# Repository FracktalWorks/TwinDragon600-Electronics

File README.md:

# TwinDragon600-Electronics

### For the Combination of BTT Manta M5P + BTT CB1 + BTT EBB36 + MKS Gen L V2.1

Electronic description, pinout and manuals for the electronics used in Twin Dragon 600

Pin Configurations, jumper selection, CanBus and multi-MCU wiring to BTT CB1 embedded onto BTT Manta M5P for Twin Dragon 600

Components used:
1. BTT Manta M5P - 1
2. BTT CB1 (embed onto BTT Manta M5P) - 1
3. BTT EBB36 Can Module/Toolboard - 2
4. TMC5160 Stepper drivers - 5
5. MKS Gen L V2.1 - 1
6. TMC2209 stepper drivers - 2 (On the MKS GenL) + 2 (Present on the BTT EBB36's)
7. BTT HDMI5 Touch Display

### For the Combination of BTT Manta M8P + BTT CB1 + RP2040 based toolboard

Pin Configurations, jumper selection, CanBus and multi-MCU wiring to BTT CB1 embedded onto BTT Manta M8P for Twin Dragon 600

Components used:
1. BTT Manta M8P - 1
2. BTT CB1 (embed onto BTT Manta M8P) - 1
3. RP2040 based Can Module/Toolboard - 2
4. TMC5160 Stepper drivers - 5
5. TMC2209 stepper drivers - 2 (On the MKS GenL) + 2 (Present on the Toolboards)
6. BTT HDMI5 Touch Display

## Setting up BTT Manta M5P + BTT CB1 + BTT EBB36 + MKS Gen L V2.1

### Initial Preparation

At the Initial stage, when needed to only access the CB1 module with USB power supply, a jumper is to be placed in the slot mentioned as 'VUSB' present between the micro HDMI port and the SOC-SD card slot.

This should not be inserted when the board is supplied with 24V and fully functioning.

### Other Initial preparation and setting up jumpers

#### TMC Driver SPI Mode

The first row are the defined pin for the drivers, which are either high or low when shorted or unshorted to establish different mode of communication. The second row are defined with the SPI modes, with the namings of 'MISO', 'CS', 'SCK' and 'MOSI' when read from left to right. Since we use the TMC5160 driver, it specifically operates only on the SPI mode. Insert the jumpers corresponding to its parallel pins only on the 1st and the 2nd row as shown in the image.

#### Driver Voltage selection

Since the TMC5160 operates only on SPI mode, which is specifically for achieving faster communication and higher speeds, it needs an operating voltage of around 48V. The manta M5P has seperte pins for regular voltage of 24V and high voltage of 48V, that is to be jumped to the common pin of voltage supply to the drivers. We jump the HV pin in the left to the middle pin of supply in order to provide 48V to the drivers, as shown in the image above.

#### Setting up jumper for probe activation

The pin for probe used here is the IND-probe pin on Manta M5P, and the jumper is placed on the two pins beside the probe pins as shown in the image above, to enable 24V supply to the ABL board.

#### Setting up Jumper for CANBUS communication

At the bottom-left corner of the board, a small jumper is to be placed on the pins that mention '120R' depicting the 120 ohms resistance that is applied on the CAN Low and High communication pins. This is a crucial pin for the setting up of the CAN communication of the motherboard and toolboard.

## Setting up of BTT EBB36 CAN module/Toolboard

### Initial preparation

After the motherboard is powered on, the yellow-green LED1 lights will light up, indicating a normal power supply. The VUSB on the right side of the board is the power selection terminal. Only when using USB to supply power to the motherboard or need to supply power through USB, do you need to use the jumper cap to connect VUSB.

#### Setting up Jumper for CANBUS communication

Similar to the BTT Manta M5P, the Support communication via CAN or USB. The terminal resistor 120R of CAN can be selected through a jumper cap, and it reserves a CAN expansion interface.

#### Placing of Heatsink

Place the Heatsink onto the TMC2209 driver chip present on the board which is already embedded onto it as shown in the image above.

## Setting up of MKS GenL V2.1 for side extruder motors

### Setting up jumpers for enabling UART mode

Since we use the TMC2209 for the side extruder motors similar to the main extruder motors, we set the drivers in UART mode

## Wiring and Connections

The overall connections of all the Electrical and Electronic components are present in the image above

### BTT Manta M5P Pin connections

### EBB36 Pin connections

The setting up of CANBUS communication in the right angle to avoid confusion

### MKS GenL V2.1 Pin Conections

In the above image, the pin connections of side extruder motors are given, along with additional ports for the extruder filament sensors

## Setting up BTT Manta M8P + BTT CB1 + RP2040 based toolboard

### Initial Preparation

At the Initial stage, when needed to only access the CB1 module with USB power supply, a jumper is to be placed in the slot mentioned as 'VUSB' present behind the Type-C port. After the M8P motherboard is powered on, the D32 red light on the left side of the MCU will light up, indicating that the power supply is normal.

### Other Initial preparation and setting up jumpers

#### TMC Driver SPI Mode

The first row are the defined pin for the drivers, which are either high or low when shorted or unshorted to establish different mode of communication. The second row are defined with the SPI modes, with the namings of 'MISO', 'CS', 'SCK' and 'MOSI' when read from left to right. Since we use the TMC5160 driver, it specifically operates only on the SPI mode. Insert the jumpers corresponding to its parallel pins only on the 1st and the 2nd row as shown in the image.

#### TMC Driver UART Mode

The given set of pin to short is the CS pin that enables only the uart mode.

#### Driver Voltage selection

For High Voltage selection(48V):

Since the TMC5160 operates only on SPI mode, which is specifically for achieving faster communication and higher speeds, it needs an operating voltage of around 48V. The manta M8P has seperte pins for regular voltage of 24V and high voltage of 48V, that is to be jumped to the common pin of voltage supply to the drivers. We jump the HV pin in the left to the middle pin of supply in order to provide 48V to the drivers, as shown in the image above.

For normal Voltage selection (24V):

This voltage selection can be used when using a regular TMC2209 on the UART mode

#### Setting up jumper for probe activation

The pin for probe used here is the IND-probe pin on Manta M8P, and the jumper is placed on the two pins beside the probe pins as shown in the image above, to enable 24V supply to the ABL board.

#### Setting up Jumper for CANBUS communication

At the top of the two CAN pins, a small jumper is to be placed on the pins that mention '120R' depicting the 120 ohms resistance that is applied on the CAN Low and High communication pins. This is a crucial pin for the setting up of the CAN communication of the motherboard and toolboard.

## Setting up of RP2040 based CAN module/Toolboard

After the motherboard is powered on, the green LED light will light up, indicating a normal power supply. The VBUS on the right side of the board is the power selection terminal. Only when using USB to supply power to the motherboard or need to supply power through USB, do you need to use the jumper cap to connect VBUS.

Similar to the BTT Manta M8P, the Support communication via CAN or USB. The terminal resistor 120R of CAN can be selected through a jumper cap, and it reserves a CAN expansion interface.

## Wiring and Connections

The overall connections of all the Electrical and Electronic components are present in the image above

  ### BTT Manta M8P Pin connections

## Setting up BTT Manta M8P V2.0 + RPi CM4 + RP2040 based toolboard

After powering on the M8P, the LED on the bottom left corner will light up to indicate normal power supply. The VUSB jumper in the center is for selecting power - it should only be shorted when powering the board via USB or supplying power out via USB.

### Other Initial preparation and setting up jumpers

#### TMC Driver SPI Mode

The first row are the defined pin for the drivers, which are either high or low when shorted or unshorted to establish different mode of communication. The second row are defined with the SPI modes, with the namings of 'MISO', 'CS', 'SCK' and 'MOSI' when read from left to right. Since we use the TMC5160 driver, it specifically operates only on the SPI mode. Insert the jumpers corresponding to its parallel pins only on the 1st and the 2nd row as shown in the image.

#### TMC Driver UART Mode

The given set of pin to short is the CS pin that enables only the uart mode.

#### Driver Voltage selection

For High Voltage selection(48V):

Since the TMC5160 operates only on SPI mode, which is specifically for achieving faster communication and higher speeds, it needs an operating voltage of around 48V. The manta M8P has seperte pins for regular voltage of 24V and high voltage of 48V, that is to be jumped to the common pin of voltage supply to the drivers. We jump the HV pin in the left to the middle pin of supply in order to provide 48V to the drivers, as shown in the image above.

For normal Voltage selection (24V):

This voltage selection can be used when using a regular TMC2209 on the UART mode

#### Setting up jumper for probe activation

The pin for probe used here is the IND-probe pin on Manta M8P V2.0, and the jumpers are placed on the two pins beside the probe pins, and other three perpendicular pins to its right, where the top two are to jumped together to activate the probe pin, as shown in the image above, to enable 24V/5V supply to the ABL board. The three columns of the pins starting from the top are 5V, 12V, 24V Respectively.

#### Setting up Jumper for CANBUS communication

At the left of the CAN pin, a small jumper is to be placed on the pins that mention '120R' depicting the 120 ohms resistance that is applied on the CAN Low and High communication pins. This is a crucial pin for the setting up of the CAN communication of the motherboard and toolboard.

## Wiring and Connections

The overall connections of all the Electrical and Electronic components are present in the image above

### BTT Manta M8P V2.0 Pin connections

## To setup Raspeberry Pi camera Rev 1.3, interfaced with RPi CM4 and BTT Manta M8P/M5P

In order to interface the Pi camera Rev 1.3 with the RPi CM4 and BTT Manta M8P/M5P, flip the board and check for a CSI1 camera slot, which should look like the image below

Instructions to attach the camera in BTT Manta M8P V2.0

Instructions to attach the camera in BTT Manta M5P

1. Now, boot up the board (including CM4), SSH into the CM4 and open the terminal
2. We will have to download a bin file into the boot folder of the CM4, below is the command to enter into the terminal.

`sudo wget https://datasheets.raspberrypi.com/cmio/dt-blob-cam1.bin -O /boot/dt-blob.bin`

If the above command does not work, try the following command:

`sudo wget https://datasheets.raspberrypi.com/cmio/dt-blob-cam1.bin -O /boot/firmware/dt-blob.bin`

3. Now, in the terminal, enter `sudo raspi-config` and select the option '3 Interface Options    Configure connections to peripherals'. Now select the first option 'P1 Camera      Enable/disable connection to the Raspberry Pi Camera'. A pop-up would appear where it asks to enable the camera. Make sure to select <yes> and exit the portal.

4. Now, in the terminal, type in `sudo nano /boot/config.txt` and make sure the settings are enabled

   `start_x=1
   gpu_mem=128`

   Note: make sure `#camera_auto_select=1` is commented out, or else it will not work.

For more clarifications, check out 'Julia TouchUI documentation' for more settings on Pi-camera

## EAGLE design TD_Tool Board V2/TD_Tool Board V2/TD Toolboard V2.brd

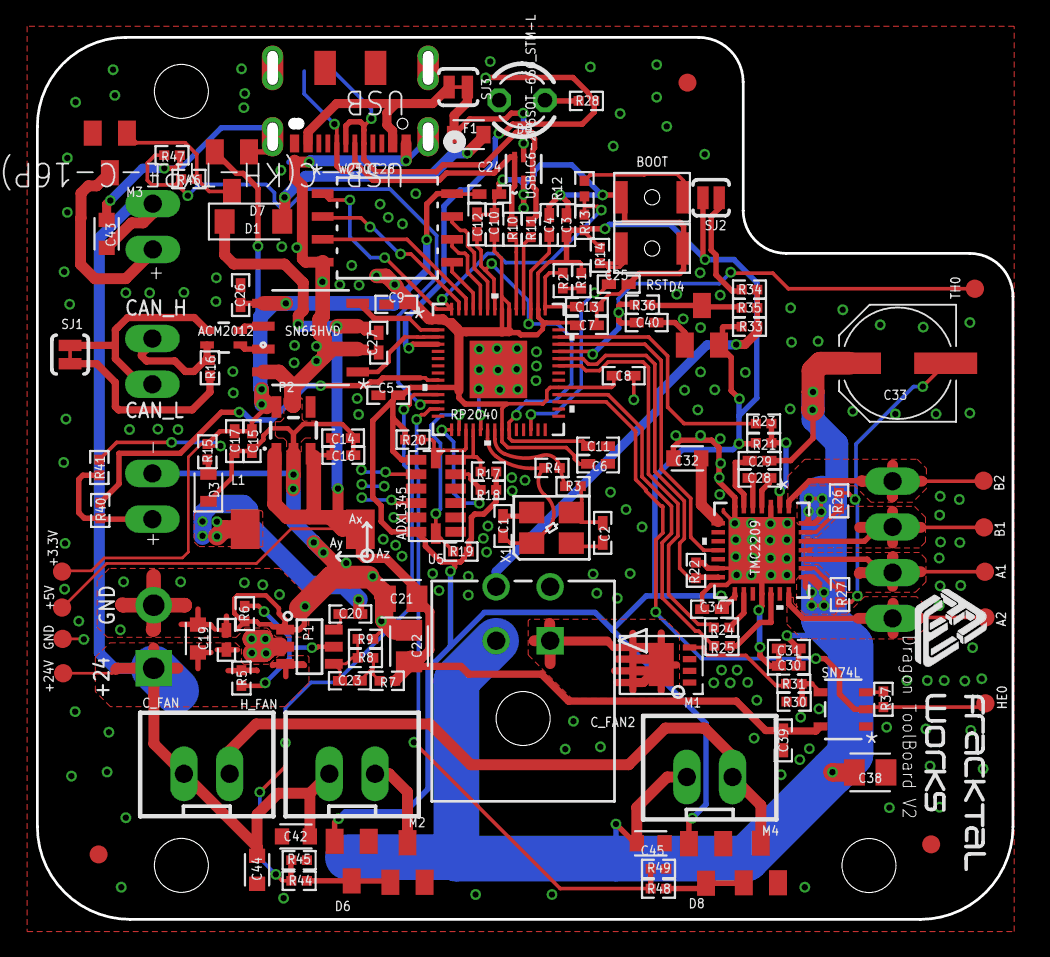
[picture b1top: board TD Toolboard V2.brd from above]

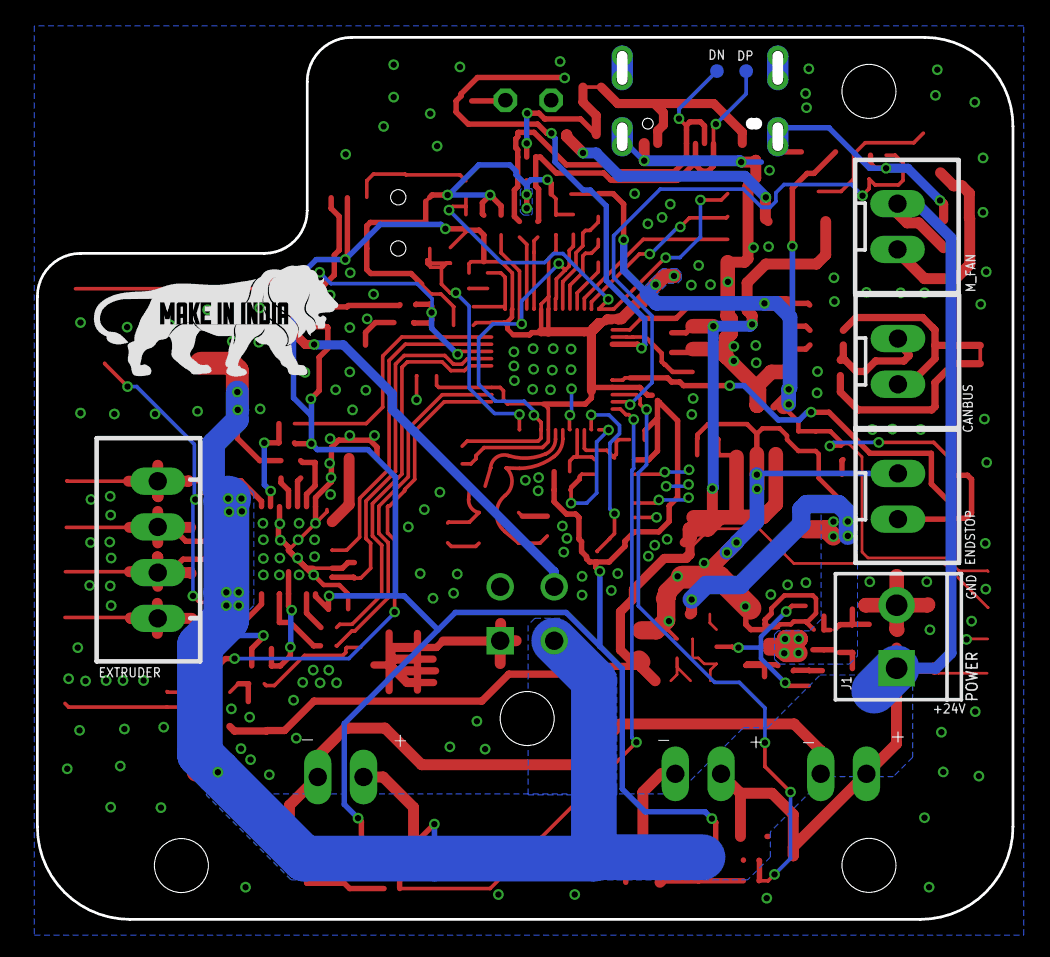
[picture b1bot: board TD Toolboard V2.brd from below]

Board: 2 copper layers, 54.2 x 49.0 mm, 140 parts (8 on the bottom side), 81 nets.

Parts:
3.3V, 5V, 24V: TEST-POINT3X4; PAD.03X.04
A1, A2: TEST-POINT3X4; PAD.03X.04
B1, B2: TEST-POINT3X4; PAD.03X.04
BOOT: B3U-1000P(M)-B
C1, C2: 30pF; CAPC1005X60
C3, C4, C13, C14, C15: 1uF; CAPC1005X60
C5, C6, C7, C8, C9, C10, C11, C12, C16, C17, C18, C20, C24, C25, C26, C27, C29, C30, C31, C34, C39, C40: 100nF; CAPC1005X60
C19: 10uF; CAPC1608X85
C21, C22, C38: 22uF; CAPC2012X110
C23: 75pF; CAPC1005X60
C28: 22nF; CAPC1005X60
C32, C42, C43, C44, C45: 4.7uF; CAPC1608X85
C33: 100uF; PANASONIC_D
CANBUS: JST-XH-02-PIN-LONG-PAD; JST-XH-02-PACKAGE-LONG-PAD
C_FAN: JST-XH-02-PIN-LONG-PAD; JST-XH-02-PACKAGE-LONG-PAD
C_FAN2: JST-XH; JST-XH-02-PACKAGE-LONG-PAD
D1: MBR0520LT1G; SODFL3718X115
D2: USBLC6-2P6SOT-666_STM-L; SOT-666_STM-L
D3: LED_G; LEDC1608X35N_FLAT-G
D4, D6, D7, D8: BAT54S; SOT23
D9: LED_G; LED3MM
ENDSTOP: JST-XH-02-PIN-LONG-PAD; JST-XH-02-PACKAGE-LONG-PAD
EXTRUDER: JST-XH-04-PIN-LONG-PAD; JST-XH-04-PACKAGE-LONG-PAD
F1: FUSE_CHIP-0603(1608-METRIC); FUSC1608X60N
FD4, FD5, FD6: FIDUCIAL; FIDUCIAL_1MM
GND: TEST-POINT3X4; PAD.03X.04
HE0: TEST-POINT3X4; PAD.03X.04
H_FAN: JST-XH-02-PIN-LONG-PAD; JST-XH-02-PACKAGE-LONG-PAD
IO1, IO2: TEST-POINT3; PAD.03X.03
J1: SCREWTERMINAL-3.5MM-2
J3: JST-MICROFIT; CON_430450400_MOL
L1: ASPI-0630HI-100M-T157X7X4; SMDRI74-680MT
L2: ACM2012; ACM2012_TDK
M1: NMOSFET_WSD3066DN33
M2, M3, M4: CJ3400; SOT23
M_FAN: JST-XH-02-PIN-LONG-PAD; JST-XH-02-PACKAGE-LONG-PAD
P1: TPS54202_BUCKCONV; SOT-23-6
P2: 3.3V; SOT23-5
R1: 200R; RESC1005X40
R2: 1R; RESC1005X40
R3, R12, R23, R24, R25, R40: 1K; RESC1005X40
R4: NO-FIT; RESC1005X40
R5: 511k; RESC1005X40
R6: 105k; RESC1005X40
R7, R15, R28: 49.9R; RESC1005X40
R8, R14: 100k; RESC1005X40
R9: 13.3k; RESC1005X40
R10, R11, R31, R44, R46, R48: 27.4R; RESC1005X40
R13: DO NOT FIT (10K); RESC1005X40
R16: 120R; RESC1005X40
R17, R18, R19, R20, R33: 4.7K; RESC1005X40
R21, R22, R37, R41: 10K; RESC1005X40
R26, R27: 220mΩ; RESC1005X40
R30, R45, R47, R49: 20K; RESC1005X40
R34: 4.12K; RESC1005X40
R35, R36: 2.37K; RESC1005X40
RST: B3U-1000P(M)-B
SJ1, SJ3: SOLDERJUMPERTRACE; SJ_2S-TRACE
SJ2: SOLDERJUMPERNO; SJ_2S-NO
TH0: TEST-POINT3X4; PAD.03X.04
U1: RP2040; IC57_RP2040-L
U2: W25Q128; SOIC_128JVSIQ_WIN-L
U3: SN65HVD; D8-L
U5: ADXL345; ADXL345_LGA14
U6: SN74L; DBV5-L
U7: TMC2209; QFN28_5X5_3X8_EPAD_TRI
U$2: MAKEININDIA
U$3: FWLOGO_SMALL
USB: USB-C(KH-TYPE-C-16P); CONN12_KH-TYPE-C-16P
X1: CRYSTAL_TAXM12M4RLBDDT2T_3225; CRYSTAL_3225

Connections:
+1.1V: C4.1, C11.1, C12.1, U1.23, U1.45, U1.50
+3.3V: 3.3V.P$1, C3.1, C5.1, C6.1, C7.1, C8.1, C9.1, C10.1, C15.1, C17.1, C24.1, C26.1, C34.1, D4.2, D6.2, D7.2, D8.2, P2.5, R1.2, R13.2, R14.2, R15.2, R17.2, R18.2, R19.2, R20.2, R21.1, R33.2, R41.1, SJ2.2, U1.1, U1.10, U1.22, U1.33, U1.42, U1.44, U1.48, U1.49, U2.8, U3.5, U5.1, U5.6, U7.15
+5V: 5V.P$1, C14.1, C16.1, C21.1, C22.1, C27.1, C39.1, D1.1, L1.2, P2.1, P2.3, R7.2, U3.3, U6.5
+24V: 24V.P$1, C18.1, C19.1, C29.1, C30.2, C31.2, C33.+, C38.1, C42.1, C43.1, C44.1, C45.1, C_FAN.1, C_FAN2.1, H_FAN.1, J1.1, J3.2, M_FAN.1, P1.3, R5.2, U7.22, U7.28
A1: A1.P$1, EXTRUDER.2, U7.24
A2: A2.P$1, EXTRUDER.1, U7.21
ADC_AVDD: C13.1, R2.1, U1.43
ADC_R: R1.1, R2.2
B1: B1.P$1, EXTRUDER.3, U7.26
B2: B2.P$1, EXTRUDER.4, U7.1
BCBOOT: C20.1, P1.6
BRA: R27.2, U7.23
BRB: R26.2, U7.27
CAN1_N: L2.2, U3.6
CAN1_P: L2.1, U3.7
CAN_N: CANBUS.2, L2.3, SJ1.1
CAN_P: CANBUS.1, L2.4, R16.1
CAN_RX: U1.2, U3.4
CAN_TX: U1.3, U3.1
CNT: R16.2, SJ1.2
DIR: R25.2, U7.19
E0_DIAG: U1.39, U7.11
E0_DIR: R25.1, U1.32
E0_EN: R23.2, U1.40
E0_STEP: R24.1, U1.36
E0_UART: R22.2, U1.37, U7.14
ENDSTOP_X: R40.1, U1.9
EX: ENDSTOP.2, R40.2, R41.2
FAN0: R44.2, R45.2, U1.11
FAN0G: D6.3, M2.1, R44.1
FAN1: R46.2, R47.2, U1.12
FAN1G: D7.3, M3.1, R46.1
FAN2: R48.2, R49.2, U1.13
FAN2G: D8.3, M4.1, R48.1
GND: BOOT.1, C1.2, C2.1, C3.2, C4.2, C5.2, C6.2, C7.2, C8.2, C9.2, C10.2, C11.2, C12.2, C13.2, C14.2, C15.2, C16.2, C17.2, C18.2, C19.2, C21.2, C22.2, C24.2, C25.1, C26.2, C27.2, C30.1, C31.1, C32.1, C33.-, C34.2, C38.2, C39.2, C40.2, C42.2, C43.2, C44.2, C45.2, D2.2, D3.C, D4.1, D6.1, D7.1, D8.1, D9.K, ENDSTOP.1, GND.P$1, J1.2, J3.3, M1.P$1, M1.P$2, M1.P$3, M2.2, M3.2, M4.2, P1.1, P2.2, R6.1, R9.1, R22.1, R26.1, R27.1, R30.1, R37.1, R45.1, R47.1, R49.1, RST.1, U1.19, U1.57, U2.4, U3.2, U3.8, U5.2, U5.4, U5.5, U6.3, U7.3, U7.7, U7.13, U7.18, U7.29, USB.1, USB.12, USB.13, USB.14, USB.15, USB.16, USB.18, USB.19, USB.20, USB.21, USB.24, USB.25, USB.26, USB.27, USB.28, USB.29, USB.37, USB.39, USB.41, USB.43, X1.P$2, X1.P$4
GPIOLED: D9.A, R28.1
HE0: HE0.P$1, R37.2, U1.31, U6.2
HE0A: R30.2, R31.2, U6.4
HE0B: M1.P$4, R31.1
HE0_PWR: J3.1, M1.P$5, M1.P$6, M1.P$7, M1.P$8, M1.P$9
LDOLED: D3.A, R15.1
LED: R28.2, U1.4
unnamed: H_FAN.2, M2.3
unnamed: M3.3, M_FAN.2
unnamed: C_FAN.2, C_FAN2.2, M4.3
OSC_IN: C1.1, R4.2, U1.20, X1.P$1
OSC_OUT: R3.2, R4.1, U1.21
QSPI_SCK: U1.52, U2.6
QSPI_SD0: U1.53, U2.5
QSPI_SD1: U1.55, U2.2
QSPI_SD2: U1.54, U2.3
QSPI_SD3: U1.51, U2.7
QSPI_SS: R12.1, R13.1, U1.56, U2.1
RESET: C25.2, R14.1, RST.2, U1.26
SPI1_CS: R19.1, U1.16, U5.7
SPI1_MISO: R18.1, U1.15, U5.12
SPI1_MOSI: R17.1, U1.18, U5.13
SPI1_SCK: R20.1, U1.17, U5.14
STEP: R24.2, U7.16
SWB: BOOT.2, R12.2
TH0: C40.1, R36.2, TH0.P$1, U1.38
TH0A: J3.4, R33.1, R34.1, R35.1
TH0B: D4.3, R35.2, R36.1
TH0C: R34.2, SJ2.1
TMC5V: C32.2, U7.8
TMCCPI: C28.1, U7.5
TMCCPO: C28.2, U7.4
TMCENN: R21.2, R23.1, U7.2
TMCVCP: C29.2, U7.6
USB1_N: D2.3, D2.4, IO1.P$1, R11.1, USB.5, USB.7
USB1_P: D2.1, D2.6, IO2.P$1, R10.1, USB.6, USB.8
USB_N: R11.2, U1.46
USB_P: R10.2, U1.47
VBUS: SJ3.2, USB.2, USB.11
VBUS1: D2.5, F1.2, SJ3.1
VBUS3: D1.2, F1.1
VRC: C23.1, R7.1, R8.2
VREGEN: P1.5, R5.1, R6.2
VREGFB: C23.2, P1.4, R8.1, R9.2
VREGO: C20.2, L1.1, P1.2
XR: C2.2, R3.1, X1.P$3

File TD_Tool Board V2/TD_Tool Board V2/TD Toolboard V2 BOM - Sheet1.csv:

Qty,Designator,Footprint,Comment,LCSC Part #,Description,Value
1,J1,SCREWTERMINAL-3.5MM-2,CONN_023.5MM,,Multi connection point. Often used as Generic Header-pin footprint for 0.1 inch spaced/style header connections,
2,"R8, R14",RESC1005X40,R_CHIP-0402(1005-METRIC),C25741,Resistor Fixed - Generic,100k
22,"C5, C6, C7, C8, C9, C10, C11, C12, C16, C17, C18, C20, C24, C25, C26, C27, C29, C30, C31, C34, C39, C40",CAPC1005X60,C_CHIP-0402(1005-METRIC),C307331,Capacitor - Generic,100nF
1,C33,PANASONIC_D,100UF-POLAR-25V-20%(ELEC),C128464,100µF polarized capacitors,100uF
1,R6,RESC1005X40,R_CHIP-0402(1005-METRIC),C2933067,Resistor Fixed - Generic,105k
4,"R21, R22, R37, R41",RESC1005X40,R_CHIP-0402(1005-METRIC),C25744,Resistor Fixed - Generic,10K
1,C19,CAPC1608X85,C_CHIP-0603(1608-METRIC),C194427,Capacitor - Generic,10uF
1,R16,RESC1005X40,R_CHIP-0402(1005-METRIC),C25079,Resistor Fixed - Generic,120R
1,R9,RESC1005X40,R_CHIP-0402(1005-METRIC),C2974007,Resistor Fixed - Generic,13.3k
6,"R3, R12, R23, R24, R25, R40",RESC1005X40,R_CHIP-0402(1005-METRIC),C25543,Resistor Fixed - Generic,1K
1,R2,RESC1005X40,R_CHIP-0402(1005-METRIC),C25086,Resistor Fixed - Generic,1R
5,"C3, C4, C13, C14, C15",CAPC1005X60,C_CHIP-0402(1005-METRIC),C52923,Capacitor - Generic,1uF
2,"R35, R36",RESC1005X40,R_CHIP-0402(1005-METRIC),C425373,Resistor Fixed - Generic,2.37K
1,R1,RESC1005X40,R_CHIP-0402(1005-METRIC),C25087,Resistor Fixed - Generic,200R
4,"R30, R45, R47, R49",RESC1005X40,R_CHIP-0402(1005-METRIC),C25765,Resistor Fixed - Generic,20K
2,"R26, R27",RESC1005X40,R_CHIP-0402(1005-METRIC),C705474,Resistor Fixed - Generic,220mΩ
1,C28,CAPC1005X60,C_CHIP-0402(1005-METRIC),C1532,Capacitor - Generic,22nF
3,"C21, C22, C38",CAPC2012X110,C_CHIP-0805(2012-METRIC),C338080,Capacitor - Generic,22uF
6,"R10, R11, R31, R44, R46, R48",RESC1005X40,R_CHIP-0402(1005-METRIC),C31439,Resistor Fixed - Generic,27.4R
1,P2,SOT23-5,V_REG_AP2112K-3.3V,C51118,AP2112 - 600mA CMOS LDO Regulator w/ Enable,3.3V
2,"C1, C2",CAPC1005X60,C_CHIP-0402(1005-METRIC),C1570,Capacitor - Generic,30pF
1,R34,RESC1005X40,R_CHIP-0402(1005-METRIC),C227106,Resistor Fixed - Generic,4.12K
5,"R17, R18, R19, R20, R33",RESC1005X40,R_CHIP-0402(1005-METRIC),C304616,Resistor Fixed - Generic,4.7K
5,"C32, C42, C43, C44, C45",CAPC1608X85,C_CHIP-0603(1608-METRIC),C162274,Capacitor - Generic,4.7uF
3,"R7, R15, R28",RESC1005X40,R_CHIP-0402(1005-METRIC),C25120,Resistor Fixed - Generic,49.9R
1,R5,RESC1005X40,R_CHIP-0402(1005-METRIC),C3037035,Resistor Fixed - Generic,511k
1,C23,CAPC1005X60,C_CHIP-0402(1005-METRIC),C37809,Capacitor - Generic,75pF
1,L2,ACM2012_TDK,ACM2012-201-2P-T002ACM2012_TDK,C3029258,,ACM2012
1,U5,ADXL345_LGA14,ADXL345BCCZ-RL,C9667,Digital Accelerometer,ADXL345
1,L1,SMDRI74-680MT,ASPI-0630HI-100M-T157X7X4,C3000391,Inductor Power Molded Wirewound 10uH 20% 3A 105mOhm DCR T/R,ASPI-0630HI-100M-T157X7X4
2,"BOOT, RST",B3U-1000P(M)-B,B3U-X000B3U-1000P(M)-B1000P(M)-B,C231329,Ultra-small Tactile Switch,B3U-1000P(M)-B
4,"D4, D6, D7, D8",SOT23,BAT54S,C47546,,BAT54S
3,"M2, M3, M4",SOT23,NMOSFET_BSS123_SOT23-GSD,C19019,N-Channel MOSFET - Popular parts,CJ3400
1,X1,CRYSTAL_3225,CRYSTAL_TAXM12M4RLBDDT2T_3225,C133334,,CRYSTAL_TAXM12M4RLBDDT2T_3225
1,R13,RESC1005X40,R_CHIP-0402(1005-METRIC),NO-FIT,Resistor Fixed - Generic,DO NOT FIT (10K)
3,"FD4, FD5, FD6",FIDUCIAL_1MM,FIDUCIAL,,"For use by pick and place machines to calibrate the vision/machine, 1mm",FIDUCIAL
1,F1,FUSC1608X60N,FUSE_CHIP-0603(1608-METRIC),C261937,Fuse - Generic,FUSE_CHIP-0603(1608-METRIC)
1,J3,CON_430450400_MOL,430450400CON_430450400_MOL,,,JST-MICROFIT
1,C_FAN2,JST-XH-02-PACKAGE-LONG-PAD,JST-XH-02-PIN-LONG-PAD,,JST XH Connector 2 Pin,JST-XH
5,"CANBUS, C_FAN, ENDSTOP, H_FAN, M_FAN",JST-XH-02-PACKAGE-LONG-PAD,JST-XH-02-PIN-LONG-PAD,,JST XH Connector 2 Pin,JST-XH-02-PIN-LONG-PAD
1,EXTRUDER,JST-XH-04-PACKAGE-LONG-PAD,JST-XH-04-PIN-LONG-PAD,,JST XH Connector 2 Pin,JST-XH-04-PIN-LONG-PAD
1,D3,LEDC1608X35N_FLAT-G,CHIP-FLAT-G_0603-0.35MM,C72043,,LED_G
1,D9,LED3MM,LED3MM,C72043,LED,LED_G
1,D1,SODFL3718X115,SCHOTTKY_MBR0520LT1GDO-219,,Schottky Diode - Popular parts,MBR0520LT1G
1,M1,NMOSFET_WSD3066DN33,NMOSFET_WSD3066DN33,C148386,,NMOSFET_WSD3066DN33
1,R4,RESC1005X40,R_CHIP-0402(1005-METRIC),NO-FIT,Resistor Fixed - Generic,NO-FIT
1,U1,IC57_RP2040-L,RP2040IC57_RP2040-L,C2040,,RP2040
1,U3,D8-L,SN65HVD1050DRD8-L,C14019,,SN65HVD
1,U6,DBV5-L,SN74LVC1G17DBVRDBV5-L,C7836,,SN74L
1,SJ2,SJ_2S-NO,SOLDERJUMPERNO,,Solder Jumper,SOLDERJUMPERNO
2,"SJ1, SJ3",SJ_2S-TRACE,SOLDERJUMPERTRACE,,Solder Jumper,SOLDERJUMPERTRACE
2,"IO1, IO2",PAD.03X.03,TEST-POINT3,,SparkFun Test Points,TEST-POINT3
10,"3.3V, 5V, 24V, A1, A2, B1, B2, GND, HE0, TH0",PAD.03X.04,TEST-POINT3X4,,SparkFun Test Points,TEST-POINT3X4
1,U7,QFN28_5X5_3X8_EPAD_TRI,TMC2209-LA-TQFN28_5X5_3X8_EPAD_TRI,C2150710,,TMC2209
1,P1,SOT-23-6,TPS54202_BUCKCONV,C191884,,TPS54202_BUCKCONV
1,USB,CONN12_KH-TYPE-C-16P,USB-C(KH-TYPE-C-16P),C709357,Shenzhen Kinghelm Elec KH-TYPE-C-16P,USB-C(KH-TYPE-C-16P)
1,D2,SOT-666_STM-L,USBLC6-2P6SOT-666_STM-L,C2827693,,USBLC6-2P6SOT-666_STM-L
1,U2,SOIC_128JVSIQ_WIN-L,W25Q128JVSIQSOIC_128JVSIQ_WIN-L,C97521,,W25Q128

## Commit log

2023-06-26 Added manuals and wiring diagram
2023-06-27 Update README.md
    Pin connections, description and initial setup of electronics has been updated with images
2023-07-24 Update README.md
    Added pin diagrams and circuits related to Manta M8P and RP2040 toolboard
2023-07-24 added M8P and THR36 datasheets
2023-07-31 added toolboard schematic
2023-08-04 Added eagle files for current progress in toolboard
2023-08-04 updated board as of 04/08/23
2023-08-05 Updated as of 05/08/23
2023-08-07 updated as of 07.08.23
2023-08-08 Create CAN_toolboard_redesign.b##
2023-08-08 Created New Schematic
2023-08-08 Buck Converter Routing
2023-08-08 Buck Changed Finalised
2023-08-08 Added LDO Components
2023-08-08 Create TD Toolboard V2.b##
2023-08-08 Added RP2040 Documentation
2023-08-08 Made Changes
2023-08-08 Routed most of the componenets to RP2040, Driver and GPIs remianing
2023-08-09 TMC routed
2023-08-09 Minor Changes
2023-08-09 Added holes, made board dimension layout, few other minor changes
2023-08-09 Placed other connectors and re arranged adxl345
2023-08-09 Finished routing all components
2023-08-09 Minor Changes for ground connectivity
2023-08-10 Fixed font sizes, added lables
2023-08-11 Fixed errors, Passed DRC, added logos
2023-08-11 Added BOM and Centroid files
2023-08-14 Increased size of 24V polygon for heater
2023-10-13 Gerber, centroids, and other minor changes
2023-10-18 minor changes in connector logic
2023-10-20 Made the required changes - renamed toolboard to V3
2023-10-20 Revert "Made the required changes - renamed toolboard to V3"
    This reverts commit 7a8e9a42dd896dbf20b13a7ad3ff12e06b196980.
2023-10-20 routed the connections for the connectors whose logic were changed
2023-10-25 updated fracktal logo with bmp
2023-12-21 Carriage Board added
2023-12-21 Added Logo
2023-12-23 Logo, Centroid, BOM, datasheet changes and addition
2024-03-02 Updated Toolboard V2 and Carriage minifit boards specs
    Toolboard and Carriage minifit board design, gerber, BOMs, centroids and connector specifications have been updated here

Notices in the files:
parts and their libraries:
SparkFun-Connectors: Licensing: Creative Commons ShareAlike 4.0 International - https://creativecommons.org/licenses/by-sa/4.0
COPYRIGHT: Copyright (C) 2023 Ultra Librarian. All rights reserved.
